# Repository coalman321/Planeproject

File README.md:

# Planeproject
DE Plane project code repository

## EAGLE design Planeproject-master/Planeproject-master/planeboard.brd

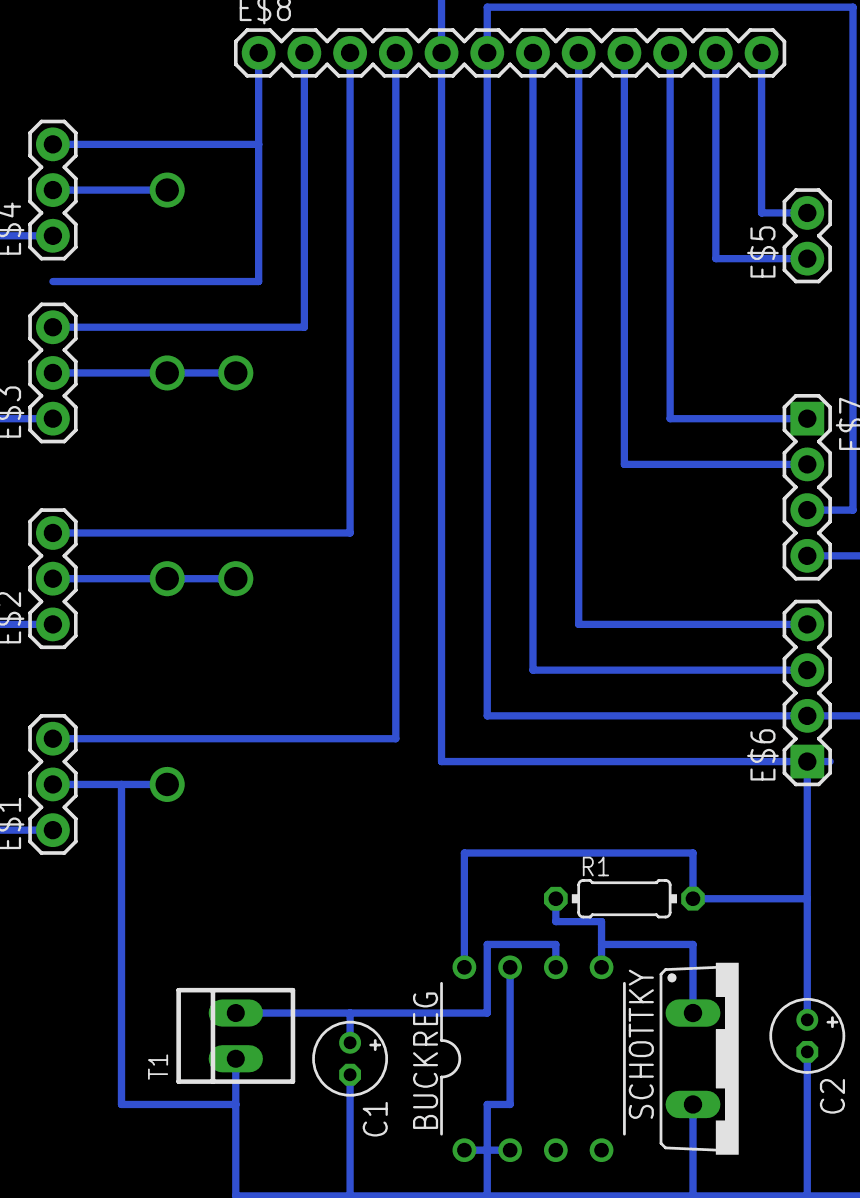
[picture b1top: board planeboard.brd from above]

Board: 2 copper layers, 14 parts (0 on the bottom side), 15 nets.

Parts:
BUCKREG: DIL08-400
C1: 22uf; E1,8-4
C2: 220uf; E1,8-4
E$1, E$2, E$3, E$4: 1X03
E$5: 1X02
E$6, E$7: 1X04
E$8: 1X12
R1: 330; 0204/7
SCHOTTKY: BR210S
T1: 22-23-2021

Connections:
S$2: E$5.2, E$8.12
S$3: BUCKREG.6, T1.2
S$4: BUCKREG.8, E$6.1, R1.2
S$5: E$5.1, E$8.11
S$6: BUCKREG.5, R1.1, SCHOTTKY.T1
S$7: E$6.3, E$8.7
S$8: E$7.1, E$8.10
S$9: E$7.2, E$8.9
S$10: E$6.4, E$8.8
S$11: E$1.1, E$2.1, E$3.1, E$4.1, E$7.4, E$8.5
S$12: E$1.3, E$8.4
S$13: E$2.3, E$8.3
S$14: E$3.3, E$8.2
S$15: E$4.3, E$8.1
S$16: BUCKREG.1, BUCKREG.2, BUCKREG.7, E$1.2, E$6.2, E$7.3, E$8.6, SCHOTTKY.T2, T1.1

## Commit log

2016-02-19 Added files via upload
2016-02-19 Create goals
2016-02-19 Update goals
2016-02-21 Started GPS library
2016-02-22 Fixed GPS library
    Made it an actual thing.
2016-02-22 Update GpsForPlane.h
    removed sofwareserial inclusion
2016-02-22 Update GpsForPlane.cpp
    Removed software serial
2016-02-22 Update GpsForPlane.cpp
    moved tiny gps inclusion
2016-02-23 updated goals
    removed spi accelerometer for start
2016-02-23 Started servos
2016-02-24 added air frame base
2016-02-24 created TO-DO list
2016-02-24 Update to-do list
2016-02-24 Software
2016-02-24 Changed things
2016-02-24 Messed with possible flying commands
2016-02-25 changed servo attachment
2016-02-25 MegaCode Update
2016-02-26 changed banking rules
2016-02-26 added roll code for control
2016-02-27 finished roll coding

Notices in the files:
parts and their libraries:
SparkFun-Connectors: Licensing: Creative Commons ShareAlike 4.0 International - https://creativecommons.org/licenses/by-sa/4.0
